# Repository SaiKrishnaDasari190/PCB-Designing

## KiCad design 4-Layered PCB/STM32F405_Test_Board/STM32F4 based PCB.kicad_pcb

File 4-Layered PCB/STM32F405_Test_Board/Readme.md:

# STM32F405 Test Board Revision-1

I have designed a 4 layered STM32F4-based PCB, which is completely with SMD (Surface-Mount Device) components (excluding Input Power Screw terminal and USB).This PCB is simple and cost efficient.

**Features 💡 :**

🔺**Input Voltage :** 4.5V - 12V (Capable of holding upto 24V)🦾

__1. STM32F405 MCU Circuit__

    🔸Decoupling Capacitors : These capacitors help stabilize the power supply for the MCU, reducing noise and voltage fluctuations.
    
    🔸VDDA Filtering : This filtering helps provide a clean and stable analog power supply for the MCU's analog components.
    
    🔸Boot Loader Switch : This allows you to switch between different firmware/bootloader versions during development or for firmware updates.
    
    🔸Crystal Oscillator : The crystal oscillator provides an accurate clock source for the MCU.
    
    🔸I2C Pull-ups : Pull-up resistors are necessary for the I2C communication lines to ensure proper voltage levels.

__2. Power Circuitry (Buck Converter)__

    🔸Reverse Polarity Protection : This feature protects the board from damage if the input power supply is connected with reverse polarity.
    
    🔸Volage Regulation : The buck converter regulates the input voltage to provide a stable and suitable voltage level for the components on the board.
    
    🔸Fusing : Fuses are used as protection devices to limit the current in case of a fault or short circuit.
    
    🔸Filtering : Filtering components, such as capacitors and inductors, help reduce noise and provide a clean power supply to the components.
    
    🔸Power Indicator LED : This LED indicates the presence of power on the board, providing a visual confirmation.

__3. Communication Protocols__

     🔸USB (Universal Serial Bus) : The USB interface allows for communication and data transfer with external devices and to dump the code as well.
     
     🔸UART (Universal Asynchronous Receiver/Transmitter) : UART is a standard asynchronous serial communication protocol used for connecting various peripherals and devices.
     
     🔸I2C (Inter-Integrated Circuit) :  I2C is a popular serial communication protocol for connecting multiple devices on a bus, using a master-slave configuration.
     
     🔸SWD (Serial Wire Debug) : SWD is a debug interface commonly used for programming and debugging microcontrollers.

Overall, This PCB design cover the essential components and features required for a STM32F4-based system.

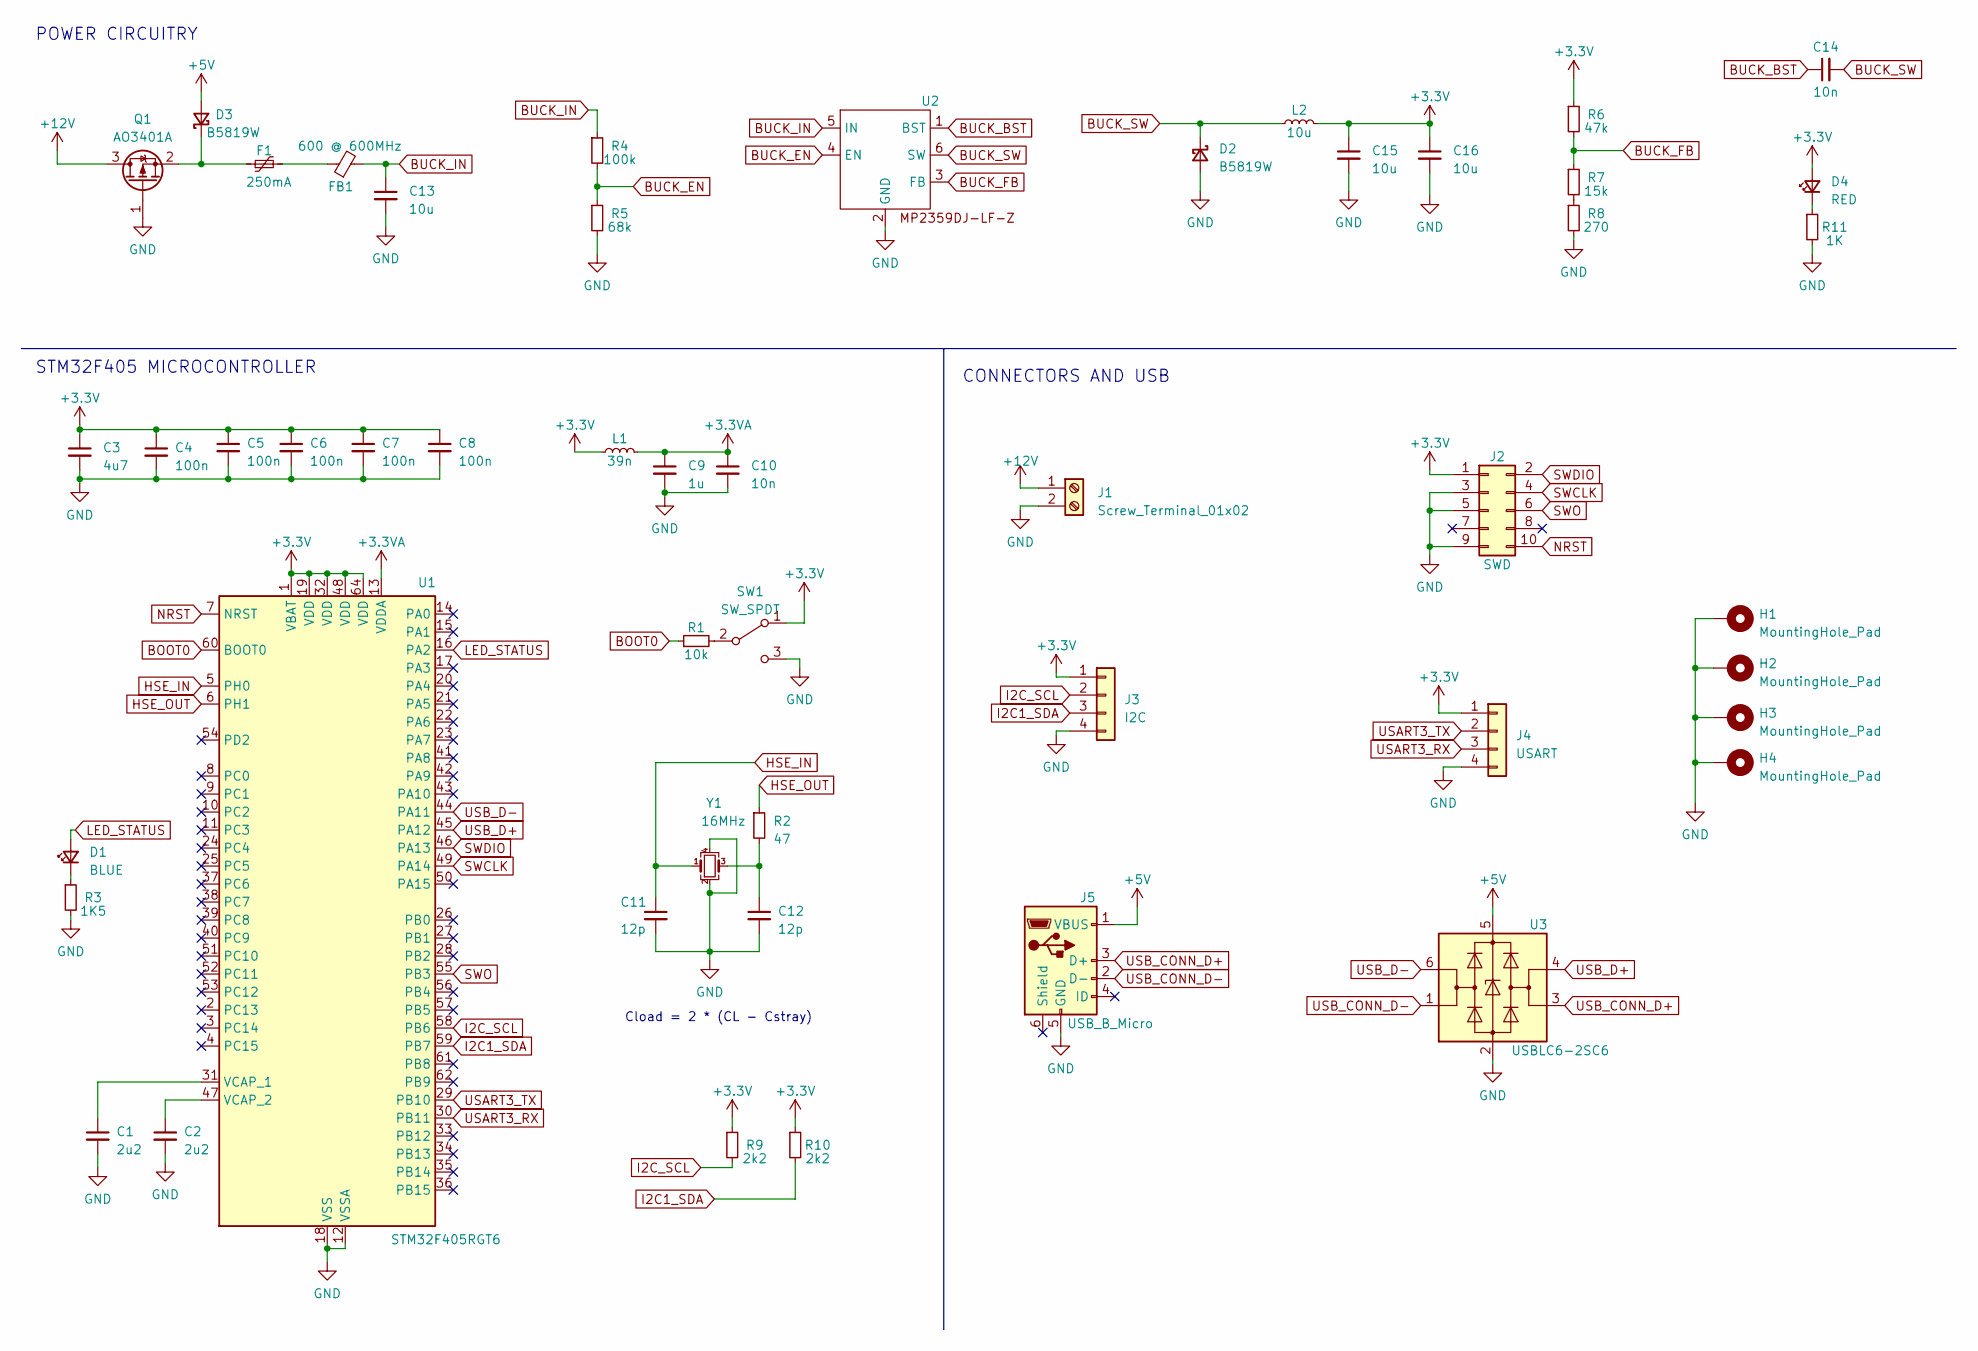
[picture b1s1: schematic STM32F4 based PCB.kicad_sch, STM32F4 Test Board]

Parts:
C1, C2: 2u2; C_0603_1608Metric
C3: 4u7; C_0603_1608Metric
C4, C5, C6, C7, C8: 100n; C_0402_1005Metric
C9: 1u; C_0402_1005Metric
C10, C14: 10n; C_0402_1005Metric
C11, C12: 12p; C_0402_1005Metric
C13, C15, C16: 10u; C_1206_3216Metric
D1: BLUE; LED_0603_1608Metric
D2, D3: B5819W; D_SOD-123
D4: RED; LED_0603_1608Metric
F1: 250mA; Fuse_1206_3216Metric
FB1: 600 @ 600MHz; L_0805_2012Metric
H1, H2, H3, H4: MountingHole_Pad; MountingHole_4.3mm_M4_Pad_Via
J1: Screw_Terminal_01x02; TerminalBlock_Phoenix_PT-1,5-2-3.5-H_1x02_P3.50mm_Horizontal
J2: SWD; PinHeader_2x05_P1.27mm_Vertical_SMD
J3: I2C; Molex_PicoBlade_53048-0410_1x04_P1.25mm_Horizontal
J4: USART; Molex_PicoBlade_53048-0410_1x04_P1.25mm_Horizontal
J5: USB_B_Micro; USB_Micro-B_Amphenol_10118194_Horizontal
L1: 39n; L_0402_1005Metric
L2: 10u; L_Sunlord_MWSA0503S
Q1: AO3401A; SOT-23
R1: 10k; R_0402_1005Metric
R2: 47; R_0402_1005Metric
R3: 1K5; R_0603_1608Metric
R4: 100k; R_0603_1608Metric
R5: 68k; R_0603_1608Metric
R6: 47k; R_0603_1608Metric
R7: 15k; R_0603_1608Metric
R8: 270; R_0603_1608Metric
R9, R10: 2k2; R_0402_1005Metric
R11: 1K; R_0603_1608Metric
SW1: SW_SPDT; SW_SPDT_PCM12
U1: STM32F405RGT6; LQFP-64_10x10mm_P0.5mm
U2: SOT-23-6
U3: USBLC6-2SC6; SOT-23-6
Y1: 16MHz; Crystal_SMD_3225-4Pin_3.2x2.5mm

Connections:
+3.3V: C3.1, C4.1, C5.1, C6.1, C7.1, C8.1, C15.1, C16.1, D4.2 (A), J2.1, J3.1, J4.1, L1.1, L2.2, R6.1, R9.1, R10.1, SW1.1 (A), U1.1 (VBAT), U1.19 (VDD), U1.32 (VDD), U1.48 (VDD), U1.64 (VDD)
+3.3VA: C9.1, C10.1, L1.2, U1.13 (VDDA)
+5V: D3.2 (A), J5.1 (VBUS), U3.5 (VBUS)
+12V: J1.1, Q1.3 (D)
BOOT0: R1.1, U1.60 (BOOT0)
BUCK_BST: C14.1, U2.1 (BST)
BUCK_EN: R4.2, R5.1, U2.4 (EN)
BUCK_FB: R6.2, R7.1, U2.3 (FB)
BUCK_IN: C13.1, FB1.2, R4.1, U2.5 (IN)
BUCK_SW: C14.2, D2.1 (K), L2.1, U2.6 (SW)
GND: C1.2, C2.2, C3.2, C4.2, C5.2, C6.2, C7.2, C8.2, C9.2, C10.2, C11.2, C12.2, C13.2, C15.2, C16.2, D2.2 (A), H1.1, H2.1, H3.1, H4.1, J1.2, J2.3, J2.5, J2.9, J3.4, J4.4, J5.5 (GND), Q1.1 (G), R3.2, R5.2, R8.2, R11.2, SW1.3 (C), U1.12 (VSSA), U1.18 (VSS), U1.63 (VSS), U2.2 (GND), U3.2 (GND), Y1.2, Y1.4
HSE_IN: C11.1, U1.5 (PH0), Y1.1
HSE_OUT: R2.1, U1.6 (PH1)
I2C1_SDA: J3.3, R10.2, U1.59 (PB7)
I2C_SCL: J3.2, R9.2, U1.58 (PB6)
LED_STATUS: D1.2 (A), U1.16 (PA2)
NRST: J2.10, U1.7 (NRST)
unnamed: C12.1, R2.2, Y1.3
unnamed: D1.1 (K), R3.1
unnamed: D3.1 (K), F1.1, Q1.2 (S)
unnamed: D4.1 (K), R11.1
unnamed: F1.2, FB1.1
unnamed: R7.2, R8.1
unnamed: R1.2, SW1.2 (B)
unnamed: C1.1, U1.31 (VCAP_1)
unnamed: C2.1, U1.47 (VCAP_2)
SWCLK: J2.4, U1.49 (PA14)
SWDIO: J2.2, U1.46 (PA13)
SWO: J2.6, U1.55 (PB3)
USART3_RX: J4.3, U1.30 (PB11)
USART3_TX: J4.2, U1.29 (PB10)
USB_CONN_D+: J5.3 (D+), U3.3 (I/O2)
USB_CONN_D-: J5.2 (D-), U3.1 (I/O1)
USB_D+: U1.45 (PA12), U3.4 (I/O2)
USB_D-: U1.44 (PA11), U3.6 (I/O1)

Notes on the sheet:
Cload = 2 * (CL - Cstray)
STM32F405 MICROCONTROLLER
CONNECTORS AND USB
POWER CIRCUITRY

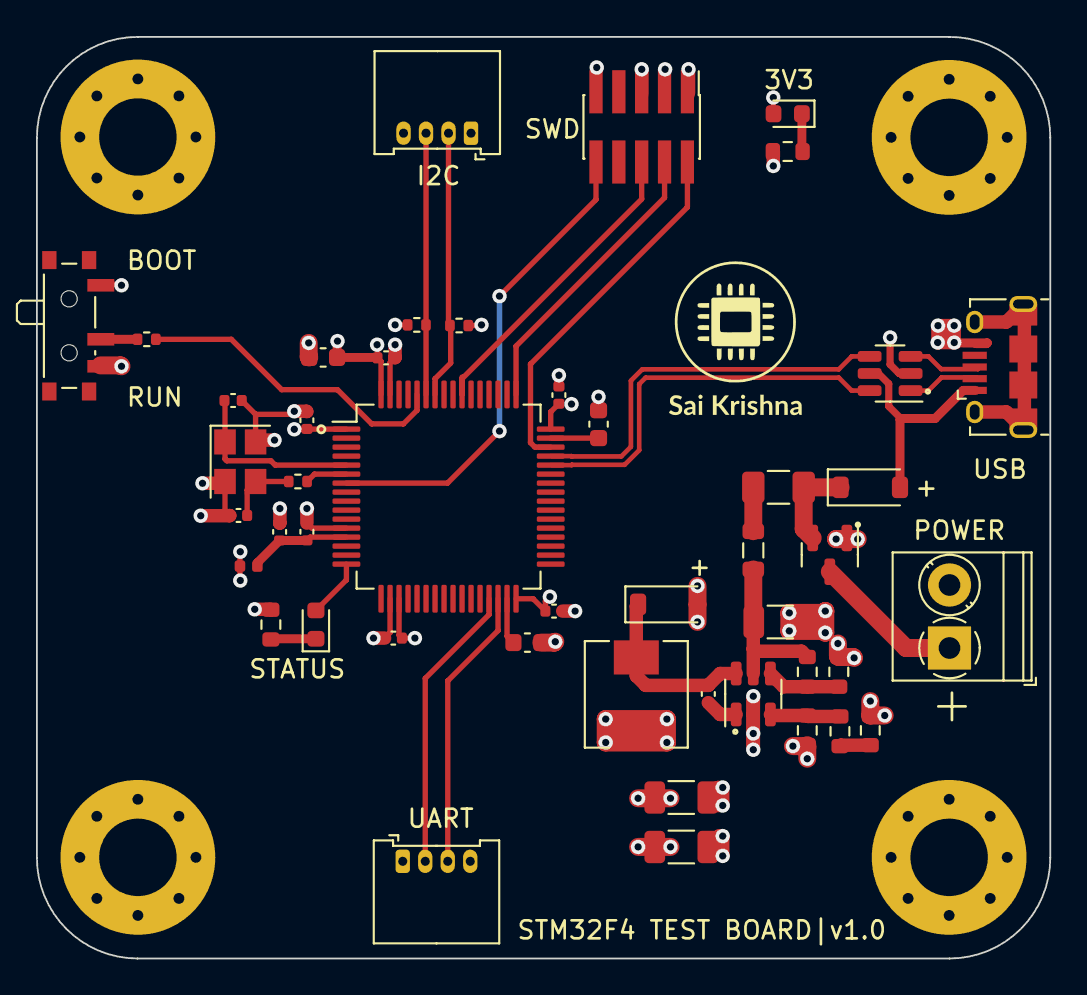
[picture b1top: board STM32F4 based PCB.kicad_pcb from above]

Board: 4 copper layers, 56.3 x 51.2 mm, 50 parts (0 on the bottom side), 35 nets.

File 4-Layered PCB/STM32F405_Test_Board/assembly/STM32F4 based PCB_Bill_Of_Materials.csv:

"Reference","Value","Footprint","LCSC Part #","Qty"
"C1, C2","2u2","Capacitor_SMD:C_0603_1608Metric","","2"
"C3","4u7","Capacitor_SMD:C_0603_1608Metric","","1"
"C4-C8","100n","Capacitor_SMD:C_0402_1005Metric","","5"
"C9","1u","Capacitor_SMD:C_0402_1005Metric","","1"
"C10, C14","10n","Capacitor_SMD:C_0402_1005Metric","","2"
"C11, C12","12p","Capacitor_SMD:C_0402_1005Metric","","2"
"C13, C15, C16","10u","Capacitor_SMD:C_1206_3216Metric","","3"
"D1","BLUE","LED_SMD:LED_0603_1608Metric","","1"
"D2, D3","B5819W","Diode_SMD:D_SOD-123","","2"
"D4","RED","LED_SMD:LED_0603_1608Metric","","1"
"F1","250mA","Fuse:Fuse_1206_3216Metric","","1"
"FB1","600 @ 600MHz","Inductor_SMD:L_0805_2012Metric","","1"
"H1-H4","MountingHole_Pad","MountingHole:MountingHole_4.3mm_M4_Pad_Via","","4"
"J1","Screw_Terminal_01x02","TerminalBlock_Phoenix:TerminalBlock_Phoenix_PT-1,5-2-3.5-H_1x02_P3.50mm_Horizontal","","1"
"J2","SWD","Connector_PinHeader_1.27mm:PinHeader_2x05_P1.27mm_Vertical_SMD","","1"
"J3","I2C","Connector_Molex:Molex_PicoBlade_53048-0410_1x04_P1.25mm_Horizontal","","1"
"J4","USART","Connector_Molex:Molex_PicoBlade_53048-0410_1x04_P1.25mm_Horizontal","","1"
"J5","USB_B_Micro","Connector_USB:USB_Micro-B_Amphenol_10118194_Horizontal","","1"
"L1","39n","Inductor_SMD:L_0402_1005Metric","","1"
"L2","10u","Inductor_SMD:L_Sunlord_MWSA0503S","","1"
"Q1","AO3401A","Package_TO_SOT_SMD:SOT-23","","1"
"R1","10k","Resistor_SMD:R_0402_1005Metric","","1"
"R2","47","Resistor_SMD:R_0402_1005Metric","","1"
"R3","1K5","Resistor_SMD:R_0603_1608Metric","","1"
"R4","100k","Resistor_SMD:R_0603_1608Metric","","1"
"R5","68k","Resistor_SMD:R_0603_1608Metric","","1"
"R6","47k","Resistor_SMD:R_0603_1608Metric","","1"
"R7","15k","Resistor_SMD:R_0603_1608Metric","","1"
"R8","270","Resistor_SMD:R_0603_1608Metric","","1"
"R9, R10","2k2","Resistor_SMD:R_0402_1005Metric","","2"
"R11","1K","Resistor_SMD:R_0603_1608Metric","","1"
"SW1","SW_SPDT","Button_Switch_SMD:SW_SPDT_PCM12","","1"
"U1","STM32F405RGT6","Package_QFP:LQFP-64_10x10mm_P0.5mm","","1"
"U2","","Package_TO_SOT_SMD:SOT-23-6","","1"
"U3","USBLC6-2SC6","Package_TO_SOT_SMD:SOT-23-6","","1"
"Y1","16MHz","Crystal:Crystal_SMD_3225-4Pin_3.2x2.5mm","","1"
